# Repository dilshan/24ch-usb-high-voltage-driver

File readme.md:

## 24-Channel USB high voltage driver

This project is a compact, driver-free USB module designed for high-voltage, medium-current output. It emphasizes ease of use, reliability, and flexibility for various control and automation applications. This module offers the following features:

- **24 independent high-voltage outputs:** Each output channel is controlled using [TPIC6B595](https://www.ti.com/lit/ds/symlink/tpic6b595.pdf) shift registers, which provide the capability for high-voltage and medium-current switching.

- **Dual power options:** Can choose between USB bus power and an external 5V supply using on-board jumpers.

- **Simple serial interface:** Communicate with the module through a virtual COM port using AT-style commands. You can easily set, get, and clear output states.

- **Device driver-free operation:** The module is recognized as a standard USB serial device (based on [CH340N](https://aitendo3.sakura.ne.jp/aitendo_data/product_img/ic/inteface/CH340N/ch340n.pdf)), meaning it requires no additional driver installation on most operating systems.

This repository includes the [schematic](https://github.com/dilshan/24ch-usb-high-voltage-driver/blob/main/design/24-ch-relay-driver-kicad.pdf), PCB design, firmware source code, and [compiled firmware](https://github.com/dilshan/24ch-usb-high-voltage-driver/releases) for this project. The complete [documentation](https://github.com/dilshan/24ch-usb-high-voltage-driver/wiki) for this project is available in the [wiki section](https://github.com/dilshan/24ch-usb-high-voltage-driver/wiki) of this repository. It includes all necessary details for producing the PCB, compiling and uploading the firmware, the command set, and more.

This is a [certified open-source hardware project](https://certification.oshwa.org/lk000015.html). All the design files, [documentation](https://github.com/dilshan/24ch-usb-high-voltage-driver/wiki), firmware source code are available to download at the project source repository. All the content of this project are distributed under the terms of the following license:

 - Hardware license: [CERN-OHL-W](https://opensource.org/license/cern-ohl-w)
 - Software license: [MIT License](https://github.com/dilshan/24ch-usb-high-voltage-driver/blob/main/LICENSE)
 - [Documentation](https://github.com/dilshan/24ch-usb-high-voltage-driver/wiki) license: [CC BY 4.0](https://creativecommons.org/licenses/by/4.0)

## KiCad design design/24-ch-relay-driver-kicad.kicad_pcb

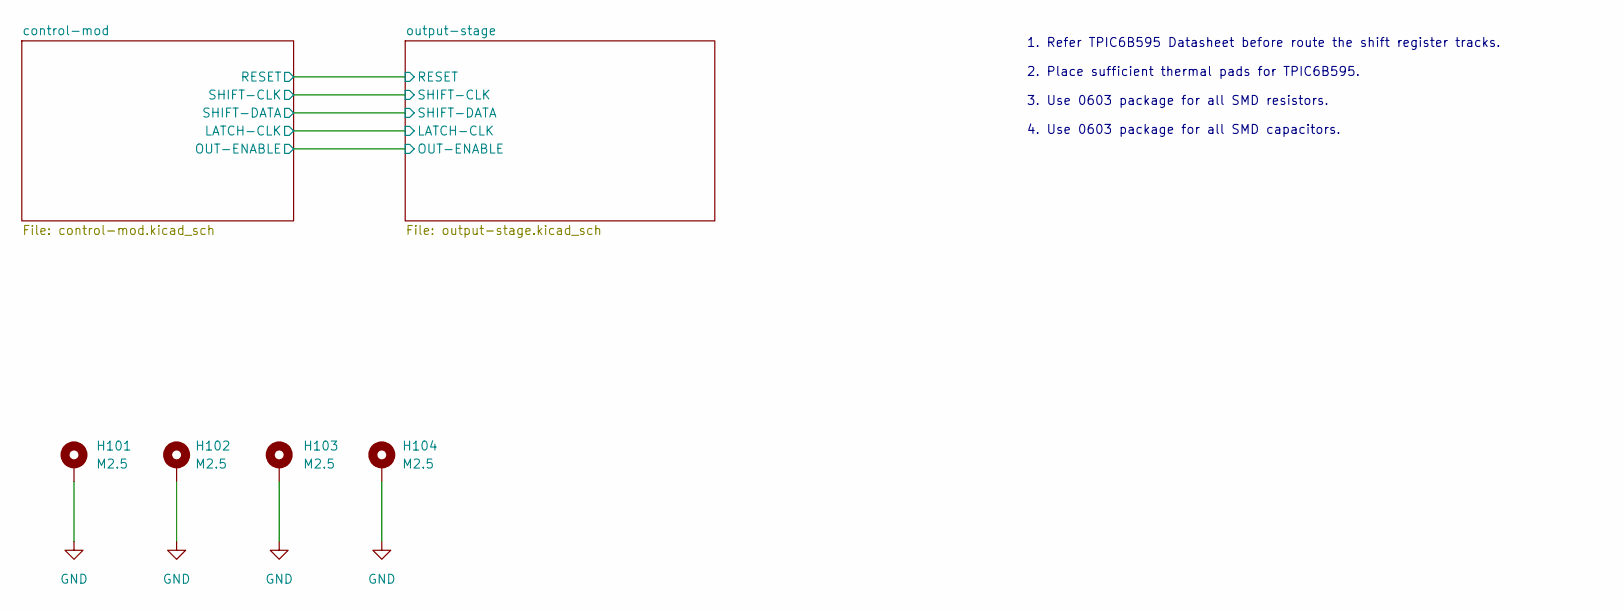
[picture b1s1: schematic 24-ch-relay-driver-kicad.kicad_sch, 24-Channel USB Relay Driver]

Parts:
H101, H102, H103, H104: M2.5; MountingHole_2.5mm_Pad

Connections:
GND: H101.1, H102.1, H103.1, H104.1; also elsewhere on the board

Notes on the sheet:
1. Refer TPIC6B595 Datasheet before route the shift register tracks. 2. Place sufficient thermal pads for TPIC6B595. 3. Use 0603 package for all SMD resistors. 4. Use 0603 package for all SMD capacitors.

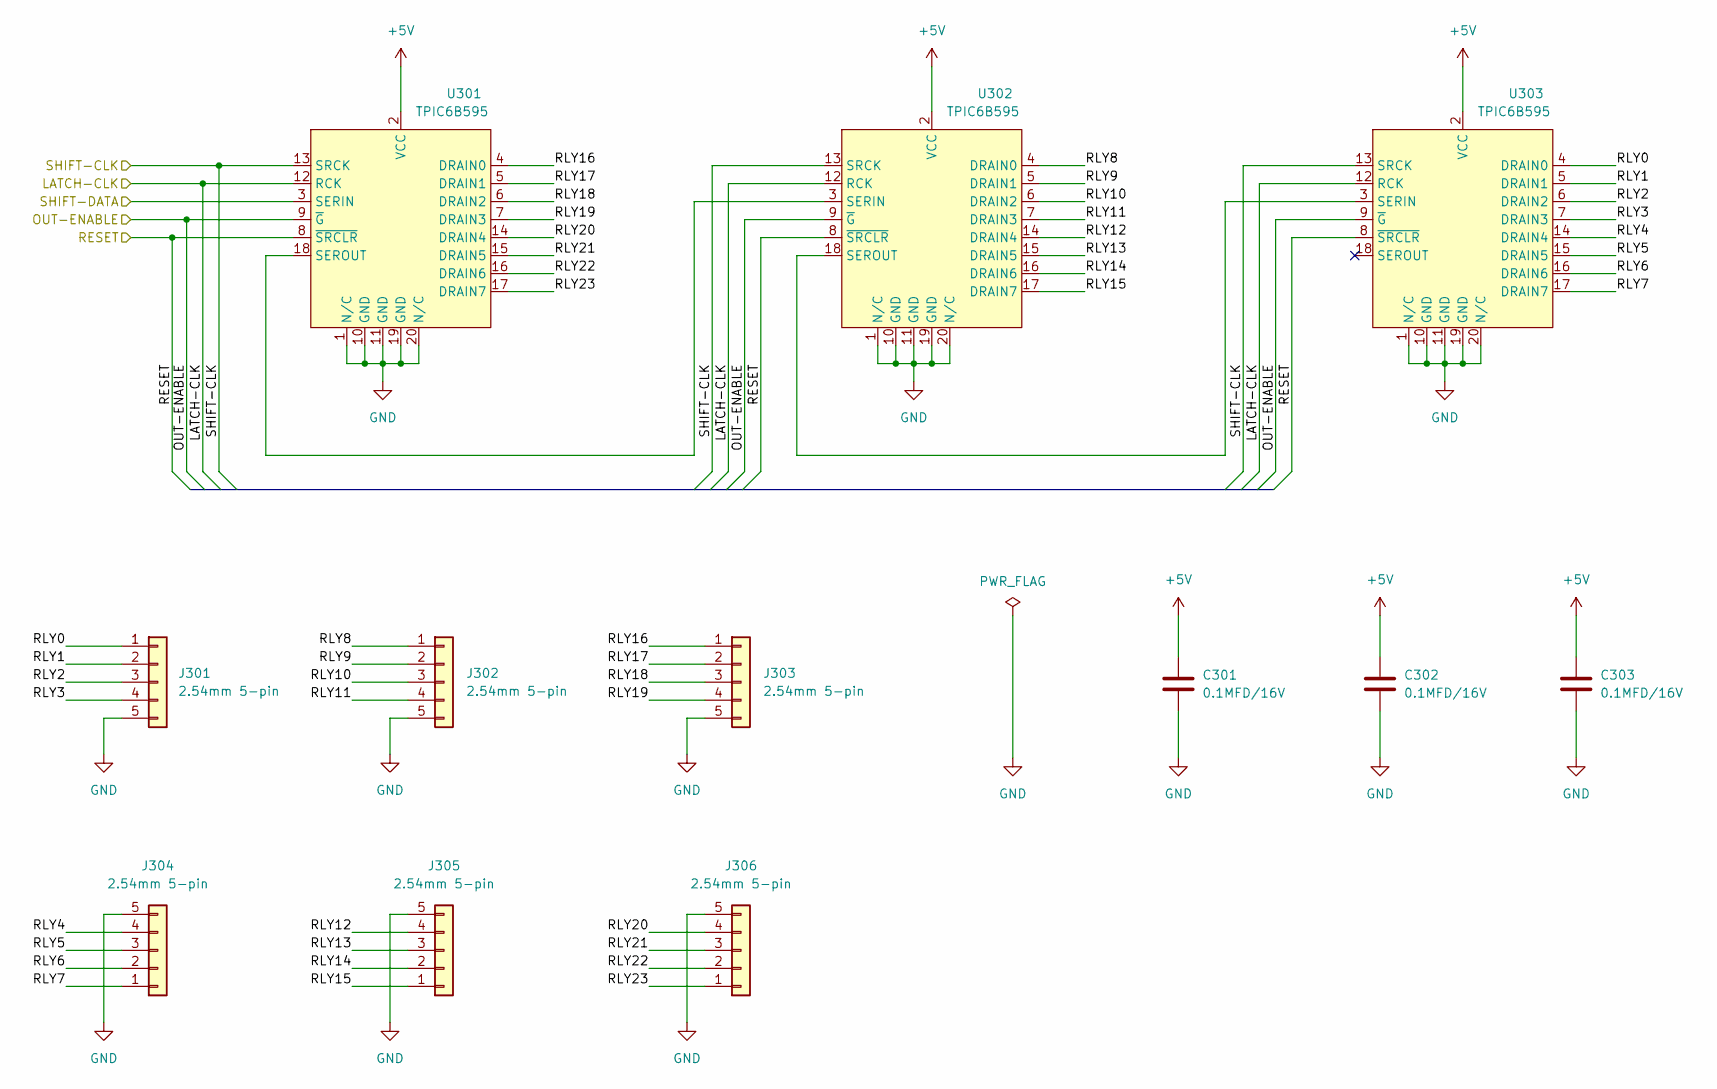
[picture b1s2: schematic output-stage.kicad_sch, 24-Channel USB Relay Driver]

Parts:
C301, C302, C303: 0.1MFD/16V; C_0603_1608Metric_Pad1.08x0.95mm_HandSolder
J301, J302, J303, J304, J305, J306: 2.54mm 5-pin; PinHeader_1x05_P2.54mm_Vertical
U301, U302, U303: TPIC6B595; SO-20_12.8x7.5mm_P1.27mm

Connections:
+5V: C301.1, C302.1, C303.1, U301.2 (VCC), U302.2 (VCC), U303.2 (VCC); also elsewhere on the board
/control-mod/SHIFT-DATA: U301.3 (SERIN); also elsewhere on the board
/output-stage/LATCH-CLK: U301.12 (RCK), U302.12 (RCK), U303.12 (RCK); also elsewhere on the board
/output-stage/OUT-ENABLE: U301.9 (~G), U302.9 (~G), U303.9 (~G); also elsewhere on the board
/output-stage/RESET: U301.8 (~SRCLR), U302.8 (~SRCLR), U303.8 (~SRCLR); also elsewhere on the board
/output-stage/RLY0: J301.1, U303.4 (DRAIN0)
/output-stage/RLY1: J301.2, U303.5 (DRAIN1)
/output-stage/RLY2: J301.3, U303.6 (DRAIN2)
/output-stage/RLY3: J301.4, U303.7 (DRAIN3)
/output-stage/RLY4: J304.4, U303.14 (DRAIN4)
/output-stage/RLY5: J304.3, U303.15 (DRAIN5)
/output-stage/RLY6: J304.2, U303.16 (DRAIN6)
/output-stage/RLY7: J304.1, U303.17 (DRAIN7)
/output-stage/RLY8: J302.1, U302.4 (DRAIN0)
/output-stage/RLY9: J302.2, U302.5 (DRAIN1)
/output-stage/RLY10: J302.3, U302.6 (DRAIN2)
/output-stage/RLY11: J302.4, U302.7 (DRAIN3)
/output-stage/RLY12: J305.4, U302.14 (DRAIN4)
/output-stage/RLY13: J305.3, U302.15 (DRAIN5)
/output-stage/RLY14: J305.2, U302.16 (DRAIN6)
/output-stage/RLY15: J305.1, U302.17 (DRAIN7)
/output-stage/RLY16: J303.1, U301.4 (DRAIN0)
/output-stage/RLY17: J303.2, U301.5 (DRAIN1)
/output-stage/RLY18: J303.3, U301.6 (DRAIN2)
/output-stage/RLY19: J303.4, U301.7 (DRAIN3)
/output-stage/RLY20: J306.4, U301.14 (DRAIN4)
/output-stage/RLY21: J306.3, U301.15 (DRAIN5)
/output-stage/RLY22: J306.2, U301.16 (DRAIN6)
/output-stage/RLY23: J306.1, U301.17 (DRAIN7)
/output-stage/SHIFT-CLK: U301.13 (SRCK), U302.13 (SRCK), U303.13 (SRCK); also elsewhere on the board
GND: C301.2, C302.2, C303.2, J301.5, J302.5, J303.5, J304.5, J305.5, J306.5, U301.1 (N/C), U301.10 (GND), U301.11 (GND), U301.19 (GND), U301.20 (N/C), U302.1 (N/C), U302.10 (GND), U302.11 (GND), U302.19 (GND), U302.20 (N/C), U303.1 (N/C), U303.10 (GND), U303.11 (GND), U303.19 (GND), U303.20 (N/C); also elsewhere on the board
unnamed: U301.18 (SEROUT), U302.3 (SERIN)
unnamed: U302.18 (SEROUT), U303.3 (SERIN)

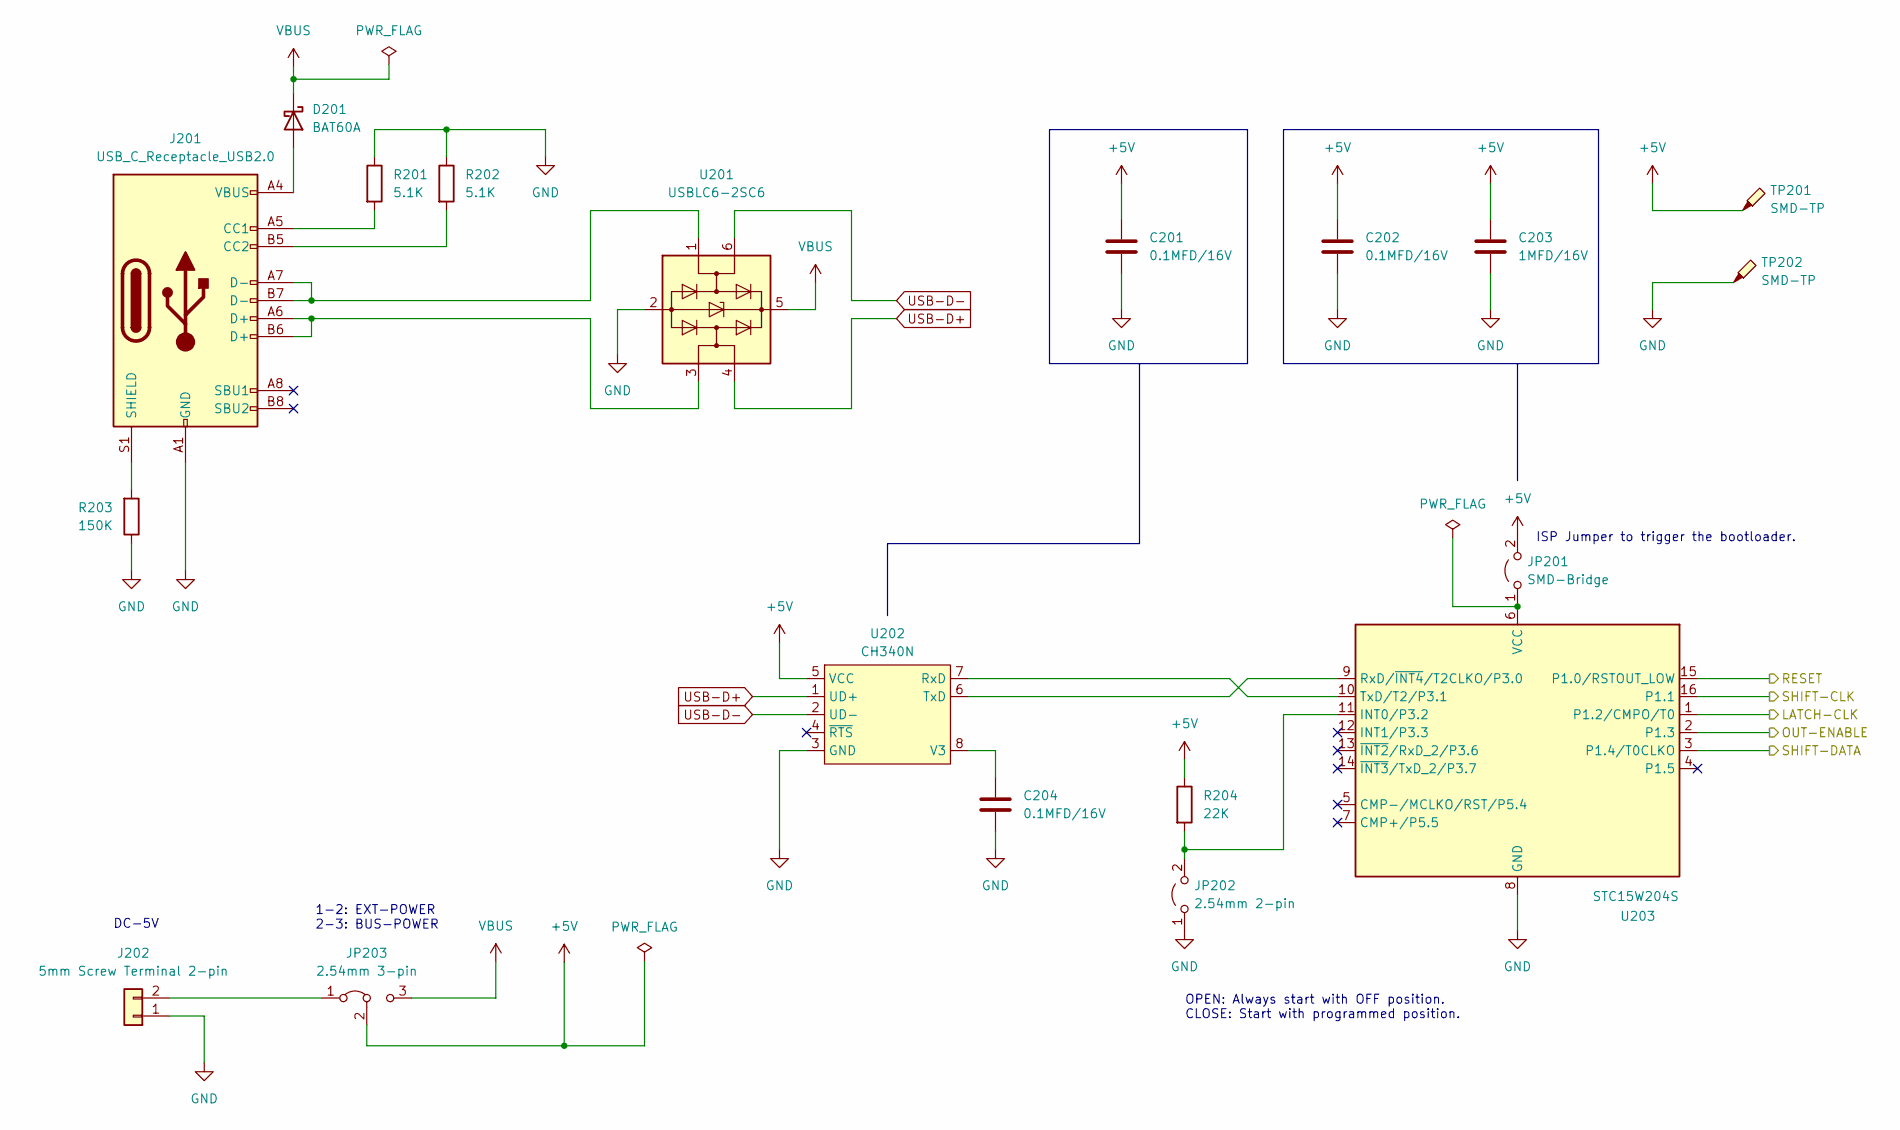
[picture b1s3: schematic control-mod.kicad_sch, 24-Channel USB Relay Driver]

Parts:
C201, C202, C204: 0.1MFD/16V; C_0603_1608Metric_Pad1.08x0.95mm_HandSolder
C203: 1MFD/16V; C_0603_1608Metric_Pad1.08x0.95mm_HandSolder
D201: BAT60A; D_SOD-323
J201: USB_C_Receptacle_USB2.0; USB_C_Receptacle_G-Switch_GT-USB-7010ASV
J202: 5mm Screw Terminal 2-pin; TerminalBlock_Phoenix_MKDS-1,5-2-5.08_1x02_P5.08mm_Horizont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
JP201: SMD-Bridge; SolderJumper-2_P1.3mm_Open_TrianglePad1.0x1.5mm
JP202: 2.54mm 2-pin; PinHeader_1x02_P2.54mm_Vertical
JP203: 2.54mm 3-pin; PinHeader_1x03_P2.54mm_Vertical
R201, R202: 5.1K; R_0603_1608Metric_Pad0.98x0.95mm_HandSolder
R203: 150K; R_0603_1608Metric_Pad0.98x0.95mm_HandSolder
R204: 22K; R_0603_1608Metric_Pad0.98x0.95mm_HandSolder
TP201, TP202: SMD-TP; TestPoint_Pad_D1.0mm
U201: USBLC6-2SC6; SOT-23-6
U202: CH340N; SOP-8_3.9x4.9mm_P1.27mm
U203: STC15W204S; STC_SOP-16_3.9x9.9mm_P1.27mm

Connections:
+5V: C201.1, C202.1, C203.1, JP201.2 (B), JP203.2 (C), R204.1, TP201.1, U202.5 (VCC); also elsewhere on the board
/control-mod/SHIFT-DATA: U203.3 (P1.4/T0CLKO); also elsewhere on the board
/output-stage/LATCH-CLK: U203.1 (P1.2/CMPO/T0); also elsewhere on the board
/output-stage/OUT-ENABLE: U203.2 (P1.3); also elsewhere on the board
/output-stage/RESET: U203.15 (P1.0/RSTOUT_LOW); also elsewhere on the board
/output-stage/SHIFT-CLK: U203.16 (P1.1); also elsewhere on the board
GND: C201.2, C202.2, C203.2, C204.2, J201.A1 (GND), J201.A12 (GND), J201.B1 (GND), J201.B12 (GND), J202.1, JP202.1 (A), R201.1, R202.1, R203.1, TP202.1, U201.2 (GND), U202.3 (GND), U203.8 (GND); also elsewhere on the board
unnamed: D201.2 (A), J201.A4 (VBUS), J201.A9 (VBUS), J201.B4 (VBUS), J201.B9 (VBUS)
unnamed: J201.A5 (CC1), R201.2
unnamed: J201.B5 (CC2), R202.2
unnamed: J201.A6 (D+), J201.B6 (D+), U201.3 (I/O2)
unnamed: J201.A7 (D-), J201.B7 (D-), U201.1 (I/O1)
unnamed: J201.S1 (SHIELD), R203.2
unnamed: J202.2, JP203.1 (A)
unnamed: JP201.1 (A), U203.6 (VCC)
unnamed: JP202.2 (B), R204.2, U203.11 (INT0/P3.2)
unnamed: U202.7 (RxD), U203.10 (TxD/T2/P3.1)
unnamed: U202.6 (TxD), U203.9 (RxD/~INT4/T2CLKO/P3.0)
unnamed: C204.1, U202.8 (V3)
USB-D+: U201.4 (I/O2), U202.1 (UD+)
USB-D-: U201.6 (I/O1), U202.2 (UD-)
VBUS: D201.1 (K), JP203.3 (B), U201.5 (VBUS)

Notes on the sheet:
ISP Jumper to trigger the bootloader.
DC-5V
1-2: EXT-POWER 2-3: BUS-POWER
OPEN: Always start with OFF position. CLOSE: Start with programmed position.

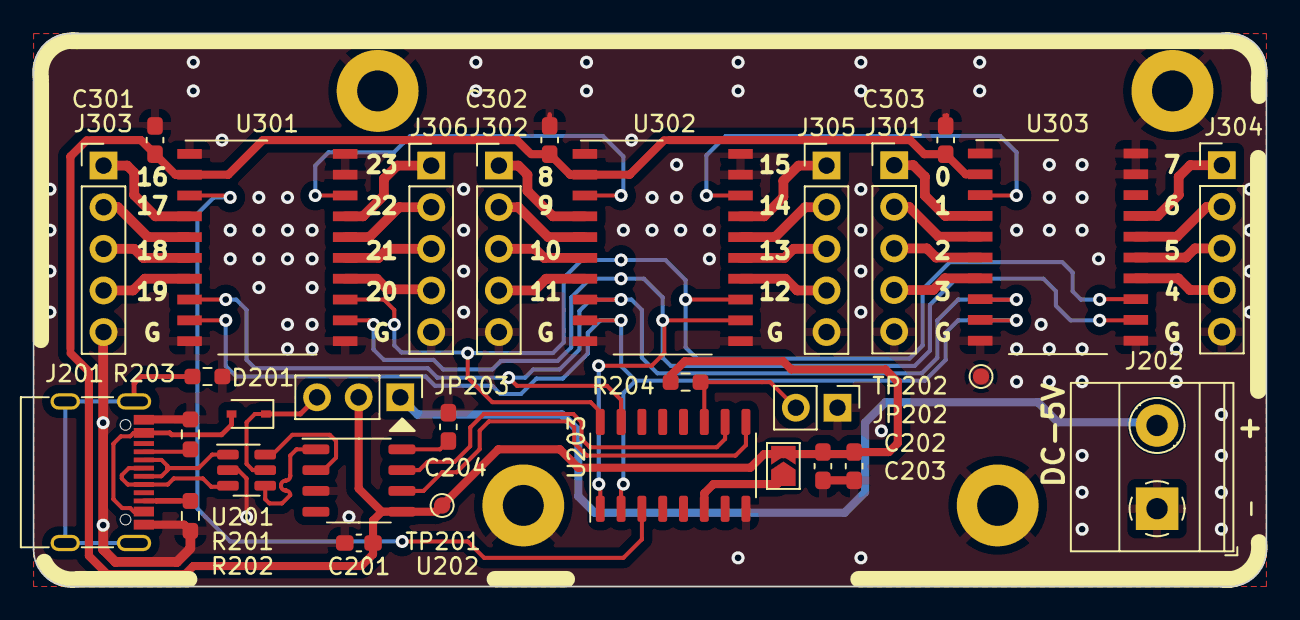
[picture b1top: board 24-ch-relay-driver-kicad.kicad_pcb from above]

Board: 2 copper layers, 75.2 x 33.8 mm, 35 parts (0 on the bottom side), 48 nets.

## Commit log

2024-01-12 Add new Simtelic logo and update version.
2024-01-12 Add gerber files for production [12/01/2024]
2024-05-05 Add initial version of documentation.
2024-05-11 Correction on Datasheet
2025-02-06 datasheet correction
2025-05-02 Clean project directory to publish.
2025-05-02 Upgrade schematic to new KiCAD version.
2025-05-02 Upgrade schematic to new SDCC version.
2025-05-02 Add initial version of readme file.
2025-05-02 Create LICENSE
2025-05-02 Fix minor issues in readme file.
2025-05-02 Fix markdown issues in serial interface document.
2025-05-02 Add PDF version of the schematic.
2025-05-02 Add project BoM.
2025-05-03 Add photo of the prototype build.
2025-05-03 Update readme.md with prototype build photo.
2025-05-03 Add datasheet links into the readme file.
2025-05-03 Add board layout drawing.
2025-05-03 Add schematics of sample interfaces.
2025-05-04 Add board dimensions.
2025-05-04 Add license and documentation information.
2025-05-04 Add links to documentation and release section.
2025-05-10 Add OSHWA certification links and logo. :ticket:
